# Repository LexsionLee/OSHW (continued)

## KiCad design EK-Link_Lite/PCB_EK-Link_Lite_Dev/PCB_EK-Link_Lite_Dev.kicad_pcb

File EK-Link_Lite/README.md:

# EK-Link Lite

此项目的目标是做一个引出部分IO到尾部，以实现制作一个某Link调试器的效果。灵感来源于网友们使用STM32最小系统板通过杜邦线连接某MCU进行调试，所以闲暇之余画了两张板。注意，EK-Link Lite是普通的双面板，而引出其他IO的Dev开发板是四层板。

该项目MCU采用的STM32F103CBT6，偶然翻出几年前留下的几枚MCU也是画这板子的原因之一。该板设计了RST按键，并引出了BOOT0、BOOT1以及SWD调试接口，同时为了迎合时代发展，USB采用了Type C接口。

## 效果图：

### EK-Link Lite

**实物：**

**3D：**

### EK-Link Lite Dev

## 基本信息：

### EK-Link Lite:

| 项目名称  | EK-Link Lite   |
| --------- | -------------- |
| PCB工艺   | 双面玻纤板     |
| PCB数量   | 1              |
| PCB尺寸   | 约59 * 23 (mm) |
| KiCad版本 | 5.1.9          |

### EK-Link Lite Dev:
| 项目名称  | EK-Link Lite Dev   |
| --------- | -------------- |
| PCB工艺   | 四层玻纤板 |
| PCB数量   | 1              |
| PCB尺寸   | 约59 * 23 (mm) |
| KiCad版本 | 5.1.9          |

## 其他事项：

暂无。

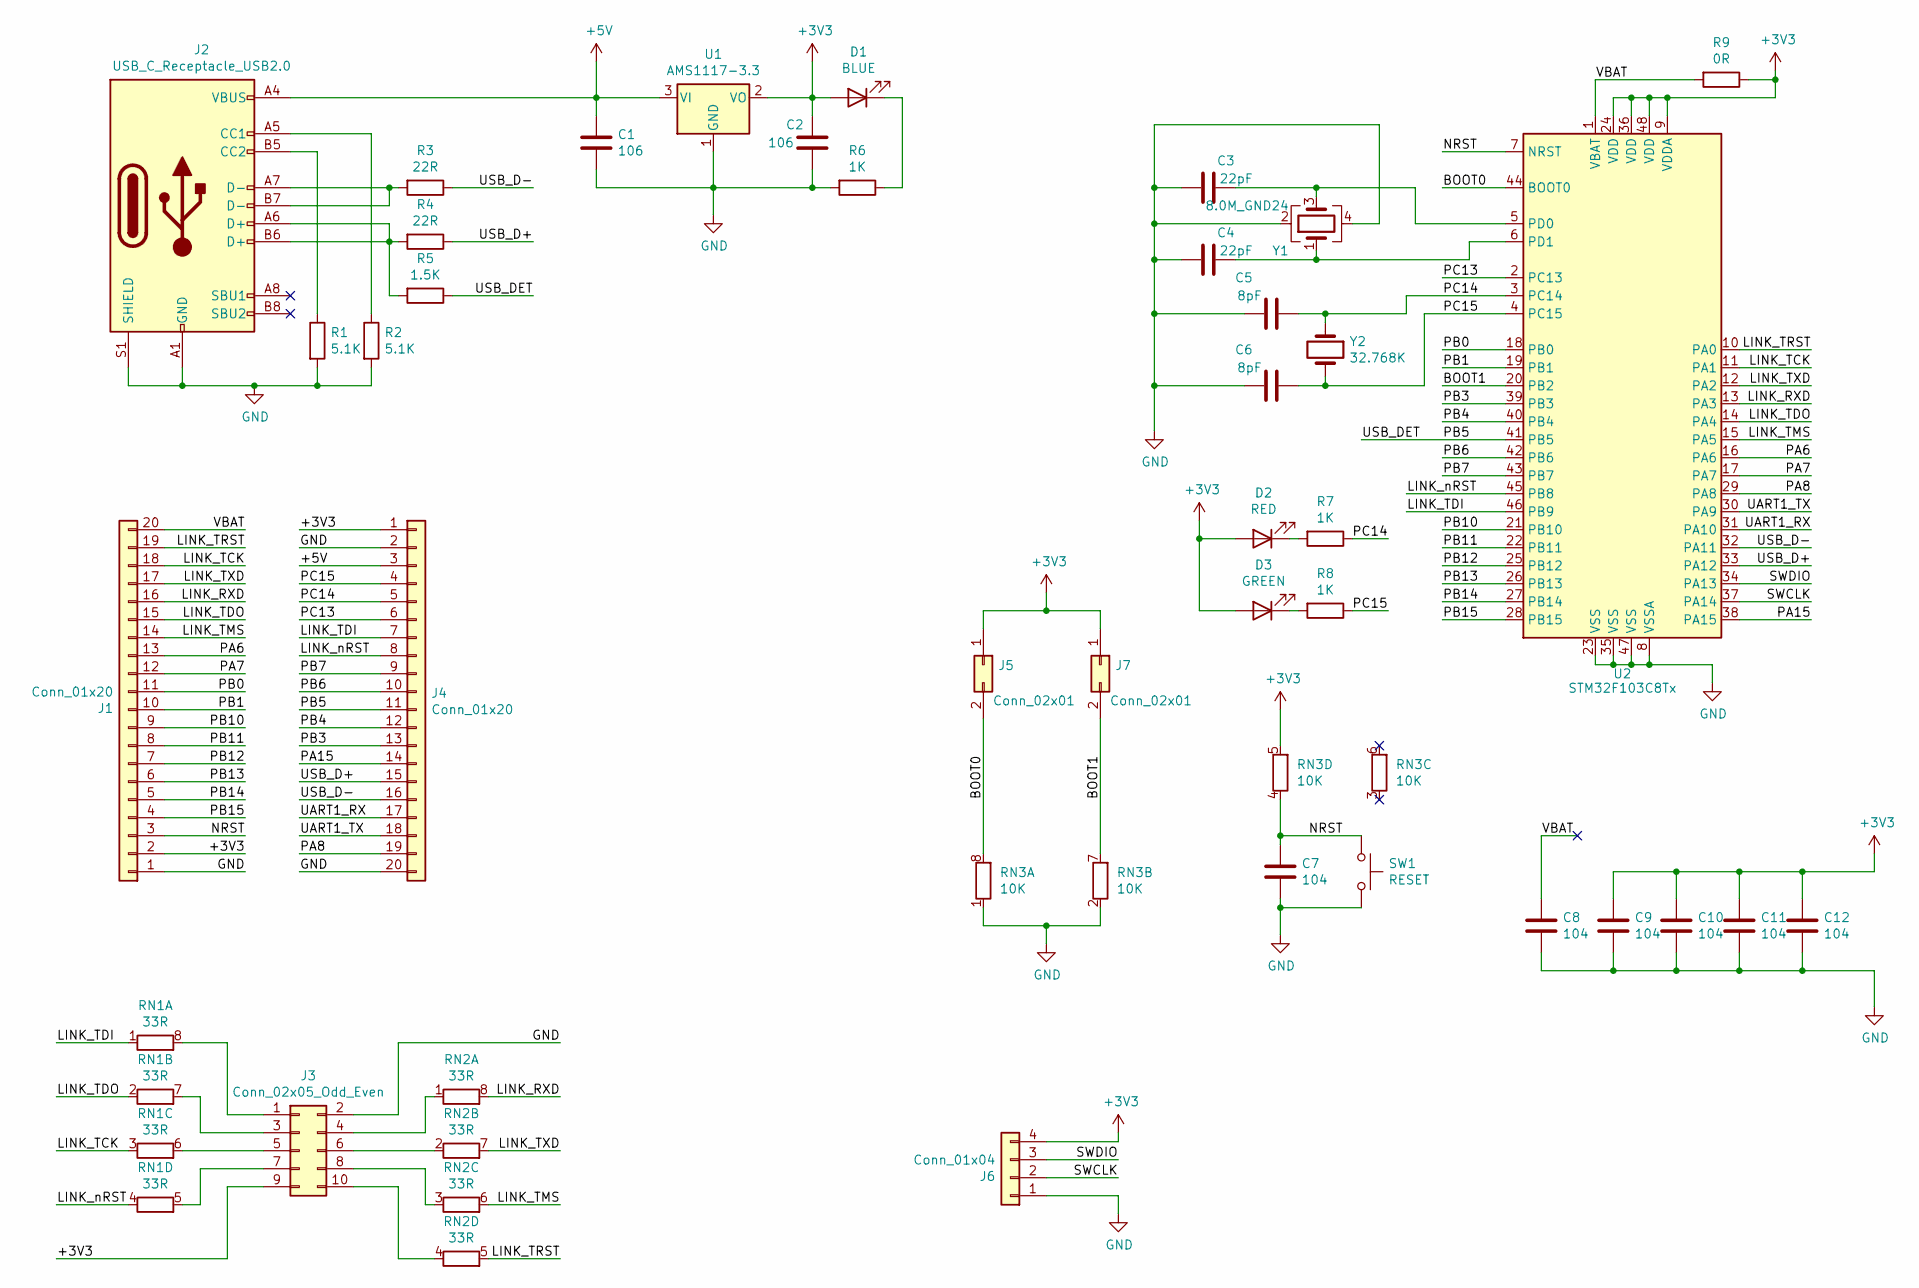
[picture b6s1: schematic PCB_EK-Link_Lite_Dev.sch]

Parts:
C1, C2: 106; C_0805_2012Metric
C3, C4: 22pF; C_0603_1608Metric
C5, C6: 8pF; C_0603_1608Metric
C7, C8, C9, C10, C11, C12: 104; C_0603_1608Metric
D1: BLUE; LED_0603_1608Metric
D2: RED; LED_0603_1608Metric
D3: GREEN; LED_0603_1608Metric
J1, J4: Conn_01x20; PinHeader_1x20_P2.54mm_Vertical
J2: USB_C_Receptacle_USB2.0; USB_C_Receptacle_Palconn_UTC16-G
J3: Conn_02x05_Odd_Even; Link_JTAG_10Pin
J5, J7: Conn_02x01; PinHeader_2x01_P2.54mm_Vertical
J6: Conn_01x04; PinHeader_1x04_P2.54mm_Vertical
R1, R2: 5.1K; R_0603_1608Metric
R3, R4: 22R; R_0402_1005Metric
R5: 1.5K; R_0603_1608Metric
R6, R7, R8: 1K; R_0603_1608Metric
R9: 0R; R_0603_1608Metric
RN1, RN2: 33R; R_Array_Concave_4x0603
RN3: 10K; R_Array_Concave_4x0603
SW1: RESET; SW_Push_SPST_NO_Alps_SKRK
U1: AMS1117-3.3; SOT-223-3_TabPin2
U2: STM32F103C8Tx; LQFP-48_7x7mm_P0.5mm
Y1: 8.0M_GND24; Oscillator_SMD_TXC_7C-4Pin_5.0x3.2mm_HandSoldering
Y2: 32.768K; Crystal_SMD_G8-2Pin_3.2x1.5mm_HandSoldering

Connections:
+3V3: C2.1, C9.1, C10.1, C11.1, C12.1, D1.2 (A), D2.2 (A), D3.2 (A), J1.2, J3.9, J4.1, J5.1, J6.4, J7.1, R9.1, RN3.5 (R4.2), U1.2 (VO), U2.9 (VDDA), U2.24 (VDD), U2.36 (VDD), U2.48 (VDD)
+5V: C1.1, J2.A4 (VBUS), J2.A9 (VBUS), J2.B4 (VBUS), J2.B9 (VBUS), J4.3, U1.3 (VI)
/BOOT0: J5.2, RN3.8 (R1.2), U2.44 (BOOT0)
/BOOT1: J7.2, RN3.7 (R2.2), U2.20 (PB2)
/LINK_RXD: J1.16, RN2.8 (R1.2), U2.13 (PA3)
/LINK_TCK: J1.18, RN1.3 (R3.1), U2.11 (PA1)
/LINK_TDI: J4.7, RN1.1 (R1.1), U2.46 (PB9)
/LINK_TDO: J1.15, RN1.2 (R2.1), U2.14 (PA4)
/LINK_TMS: J1.14, RN2.6 (R3.2), U2.15 (PA5)
/LINK_TRST: J1.19, RN2.5 (R4.2), U2.10 (PA0)
/LINK_TXD: J1.17, RN2.7 (R2.2), U2.12 (PA2)
/LINK_nRST: J4.8, RN1.4 (R4.1), U2.45 (PB8)
/NRST: C7.1, J1.3, RN3.4 (R4.1), SW1.1, U2.7 (NRST)
/PA6: J1.13, U2.16 (PA6)
/PA7: J1.12, U2.17 (PA7)
/PA8: J4.19, U2.29 (PA8)
/PA15: J4.14, U2.38 (PA15)
/PB0: J1.11, U2.18 (PB0)
/PB1: J1.10, U2.19 (PB1)
/PB3: J4.13, U2.39 (PB3)
/PB4: J4.12, U2.40 (PB4)
/PB5: J4.11, R5.1, U2.41 (PB5)
/PB6: J4.10, U2.42 (PB6)
/PB7: J4.9, U2.43 (PB7)
/PB10: J1.9, U2.21 (PB10)
/PB11: J1.8, U2.22 (PB11)
/PB12: J1.7, U2.25 (PB12)
/PB13: J1.6, U2.26 (PB13)
/PB14: J1.5, U2.27 (PB14)
/PB15: J1.4, U2.28 (PB15)
/PC13: J4.6, U2.2 (PC13)
/PC14: C5.2, J4.5, R7.1, U2.3 (PC14), Y2.1
/PC15: C6.2, J4.4, R8.1, U2.4 (PC15), Y2.2
/SWCLK: J6.2, U2.37 (PA14)
/SWDIO: J6.3, U2.34 (PA13)
/UART1_RX: J4.17, U2.31 (PA10)
/UART1_TX: J4.18, U2.30 (PA9)
/USB_D+: J4.15, R4.1, U2.33 (PA12)
/USB_D-: J4.16, R3.1, U2.32 (PA11)
/VBAT: C8.1, J1.20, R9.2, U2.1 (VBAT)
GND: C1.2, C2.2, C3.1, C4.1, C5.1, C6.1, C7.2, C8.2, C9.2, C10.2, C11.2, C12.2, J1.1, J2.A1 (GND), J2.A12 (GND), J2.B1 (GND), J2.B12 (GND), J2.S1 (SHIELD), J3.2, J4.2, J4.20, J6.1, R1.2, R2.2, R6.2, RN3.1 (R1.1), RN3.2 (R2.1), SW1.2, U1.1 (GND), U2.8 (VSSA), U2.23 (VSS), U2.35 (VSS), U2.47 (VSS), Y1.2, Y1.4
unnamed: C3.2, U2.5 (PD0), Y1.3
unnamed: C4.2, U2.6 (PD1), Y1.1
unnamed: D1.1 (K), R6.1
unnamed: D2.1 (K), R7.2
unnamed: D3.1 (K), R8.2
unnamed: J2.A5 (CC1), R2.1
unnamed: J2.A6 (D+), J2.B6 (D+), R4.2, R5.2
unnamed: J2.A7 (D-), J2.B7 (D-), R3.2
unnamed: J2.B5 (CC2), R1.1
unnamed: J3.1, RN1.8 (R1.2)
unnamed: J3.3, RN1.7 (R2.2)
unnamed: J3.4, RN2.1 (R1.1)
unnamed: J3.5, RN1.6 (R3.2)
unnamed: J3.6, RN2.2 (R2.1)
unnamed: J3.7, RN1.5 (R4.2)
unnamed: J3.8, RN2.3 (R3.1)
unnamed: J3.10, RN2.4 (R4.1)

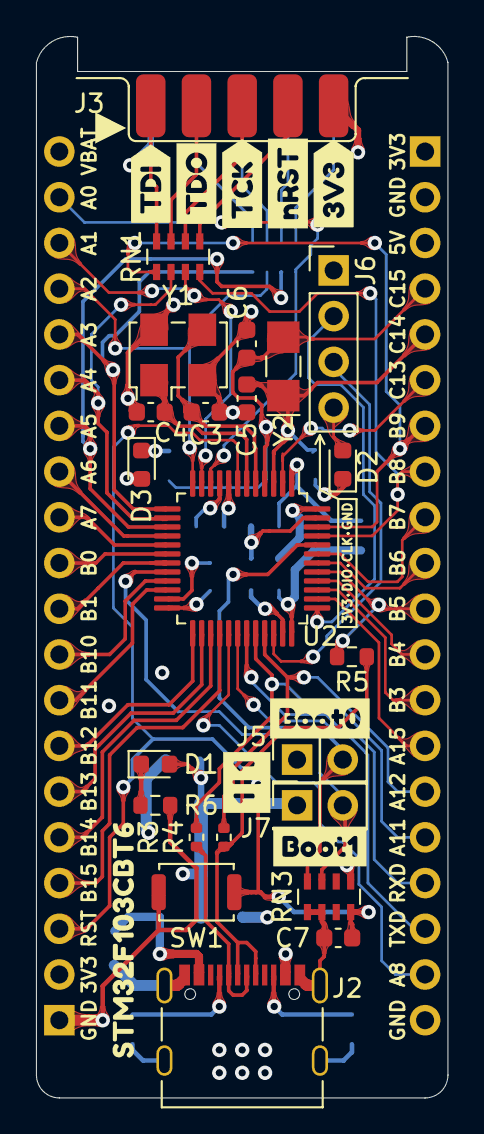
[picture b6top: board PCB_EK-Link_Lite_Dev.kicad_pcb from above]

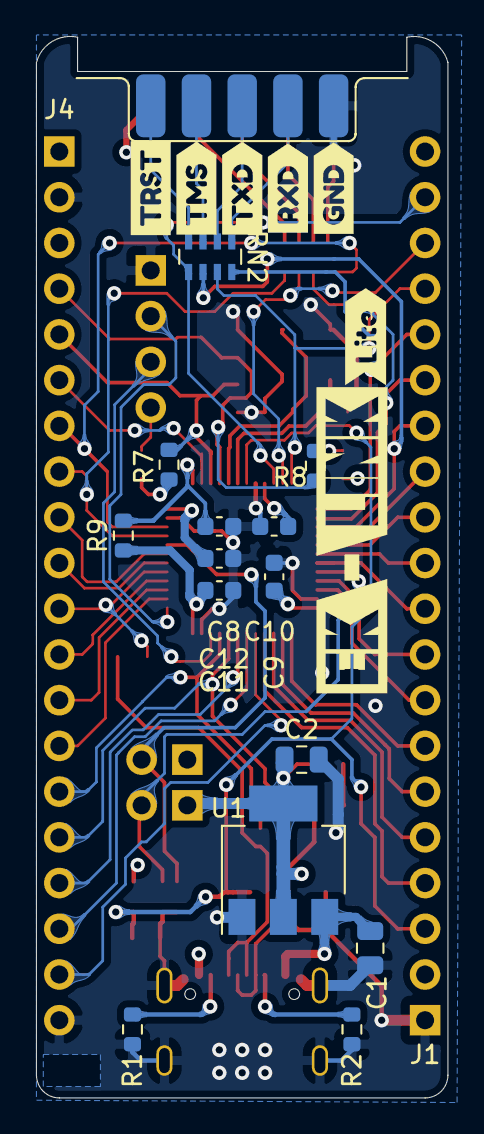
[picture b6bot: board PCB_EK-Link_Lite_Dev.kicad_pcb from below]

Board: 4 copper layers, 22.9 x 59.0 mm, 57 parts (25 on the bottom side), 58 nets.

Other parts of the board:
svg2mod, svg2mod#2, svg2mod#3, svg2mod#4, svg2mod#5, svg2mod#6, svg2mod#7, svg2mod#8, svg2mod#9, svg2mod#10, svg2mod#11, svg2mod#12, svg2mod#13, svg2mod#14, svg2mod#15, svg2mod#16, svg2mod#17, svg2mod#18: G***; label

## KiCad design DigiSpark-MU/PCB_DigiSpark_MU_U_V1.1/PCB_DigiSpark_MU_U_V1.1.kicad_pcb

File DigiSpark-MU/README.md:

# DigiSpark-MU

此项目仿制了Digistump 的 Digispark，它是一款基于ATtiny85的单片机开发板，类似于Arduino，但它更便宜、更小巧，性能也相对弱一些。通过为其编程，可模拟HID设备（如键盘），从而欺骗电脑使其认为是人在操作它，这类应用称为BadUSB。具体相关内容可以通过网络查询，此处不再赘述。

此项目命名为DigiSpark-MU，是因为对比原始项目，本项目单片机选用了QFN封装的ATtiny85-20MU而不是SOIC封装的SU。因为全球IC价格上涨的关系，SOIC封装的tiny85价格相对更高。而使用QFN封装的IC，不但价格更低，且得益于其不到1毫米的封装厚度，有望实现将芯片隐藏于层叠的PCB中。这样便可以得到比原始设计更小、更薄的设计。为了实现薄化设计，此项目舍弃了为其他电压应用准备的5V LDO，舍弃了USB取电处的防逆流二极管。

> 我才不会说是因为白嫖了立创海外代购51减50活动，Digi-Key的单片机真香。

## 效果图：

### 实物图：

### M板：

### U板（上板）：

## 基本信息：

| 项目名称  | DigiSpark-MU            |
| --------- | ----------------------- |
| PCB工艺   | 双面玻纤板              |
| PCB数量   | 2                       |
| PCB尺寸   | 约26.8 * 12 (mm)  *2PCS |
| KiCad版本 | 5.1.9                   |

## 其他事项：

PCB厚度是1.0mm。

该项目由两片PCB组成。元器件主要集中在下板上，我称其为M板；USB接触的金手、齐纳二极管指和复位按键在上板，称其为U板。项目文件有三个，ALL是所有元器件在一个原理图中，为了提供统一的原理图；M是底层PCB的设计；U是上层板的设计。Gerber文件压缩存放于对应PCB目录的Gerber目录下。

装配方式为两枚PCB分别回流焊，然后再将两枚PCB通过回流焊叠焊在一起。

其他未尽事项请参阅原始文件。

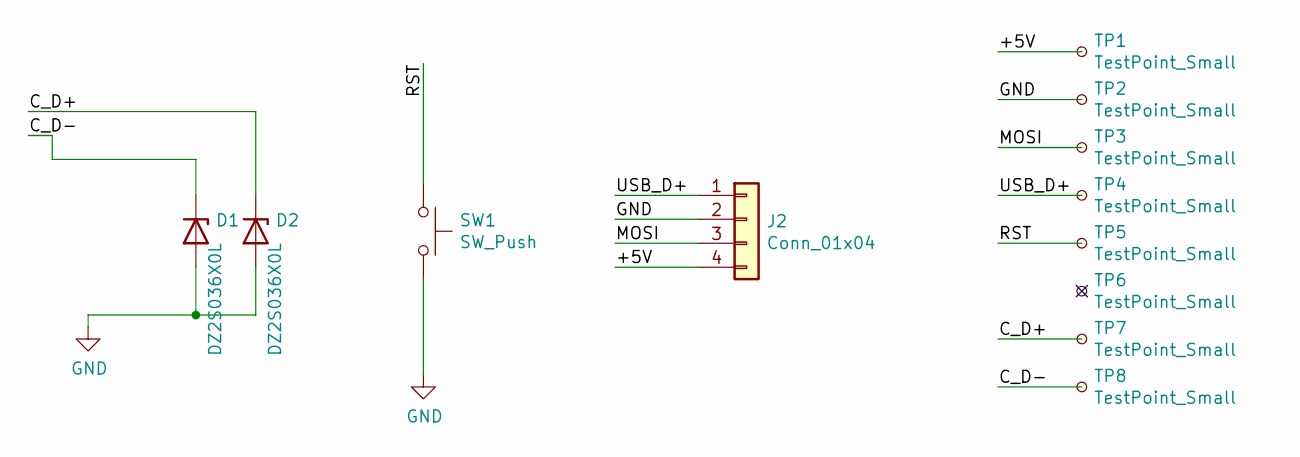
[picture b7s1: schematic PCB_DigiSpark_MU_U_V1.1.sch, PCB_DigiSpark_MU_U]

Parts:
D1, D2: DZ2S036X0L; D_SOD-523
J2: Conn_01x04; Lex_Conn_Edge_2.54-4
SW1: SW_Push; SW_SPST_SKQG_WithStem
TP1, TP2, TP3, TP4, TP5, TP6, TP7, TP8: TestPoint_Small; TestPoint_Pad_D1.0mm

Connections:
+5V: J2.4, TP1.1; also elsewhere on the board
/C_D+: D2.1 (K), TP7.1; also elsewhere on the board
/C_D-: D1.1 (K), TP8.1; also elsewhere on the board
/MOSI: J2.3, TP3.1
/RST: SW1.1, TP5.1
/USB_D+: J2.1, TP4.1
GND: D1.2 (A), D2.2 (A), J2.2, SW1.2, TP2.1; also elsewhere on the board

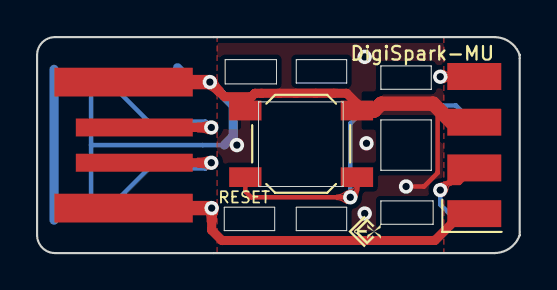
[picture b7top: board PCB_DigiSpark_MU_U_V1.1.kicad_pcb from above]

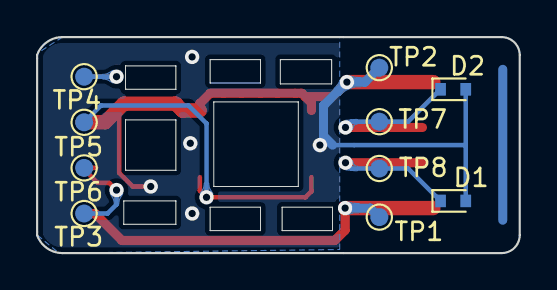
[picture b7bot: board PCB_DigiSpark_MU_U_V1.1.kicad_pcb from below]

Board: 2 copper layers, 26.8 x 12.0 mm, 13 parts (10 on the bottom side), 7 nets.

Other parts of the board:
J1: USB_A; PCBUSB_A_Male

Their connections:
+5V: J1.1; also elsewhere on the board
/C_D+: J1.3; also elsewhere on the board
/C_D-: J1.2; also elsewhere on the board
GND: J1.4; also elsewhere on the board

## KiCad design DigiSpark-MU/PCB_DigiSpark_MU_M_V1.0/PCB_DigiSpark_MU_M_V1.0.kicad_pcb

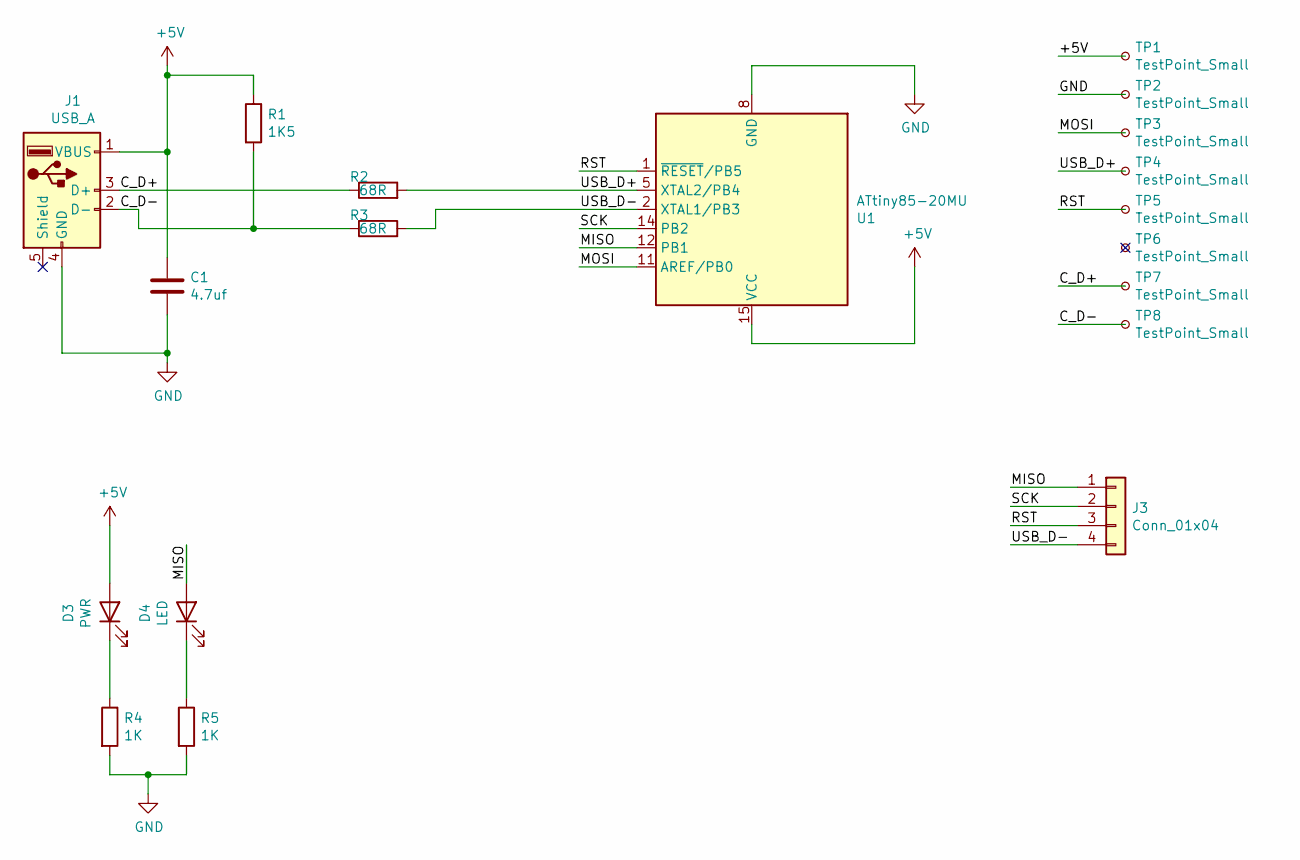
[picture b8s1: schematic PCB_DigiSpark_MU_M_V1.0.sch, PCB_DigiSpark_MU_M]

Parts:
C1: 4.7uf; C_0603_1608Metric
D3: PWR; LED_0603_1608Metric
D4: LED; LED_0603_1608Metric
J1: USB_A; PCBUSB_A_Male
J3: Conn_01x04; Lex_Conn_Edge_2.54-4
R1: 1K5; R_0603_1608Metric
R2, R3: 68R; R_0603_1608Metric
R4, R5: 1K; R_0603_1608Metric
TP1, TP2, TP3, TP4, TP5, TP6, TP7, TP8: TestPoint_Small; TestPoint_Pad_D1.0mm
U1: ATtiny85-20MU; QFN-20-1EP_4x4mm_P0.5mm_EP2.6x2.6mm

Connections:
+5V: C1.1, D3.2 (A), J1.1 (VBUS), R1.1, TP1.1, U1.15 (VCC)
/C_D+: J1.3 (D+), R2.1, TP7.1
/C_D-: J1.2 (D-), R1.2, R3.1, TP8.1
/MISO: D4.2 (A), J3.1, U1.12 (PB1)
/MOSI: TP3.1, U1.11 (AREF/PB0)
/RST: J3.3, TP5.1, U1.1 (~RESET~/PB5)
/SCK: J3.2, U1.14 (PB2)
/USB_D+: R2.2, TP4.1, U1.5 (XTAL2/PB4)
/USB_D-: J3.4, R3.2, U1.2 (XTAL1/PB3)
GND: C1.2, J1.4 (GND), R4.2, R5.2, TP2.1, U1.8 (GND), U1.21 (GND)
unnamed: D3.1 (K), R4.1
unnamed: D4.1 (K), R5.1

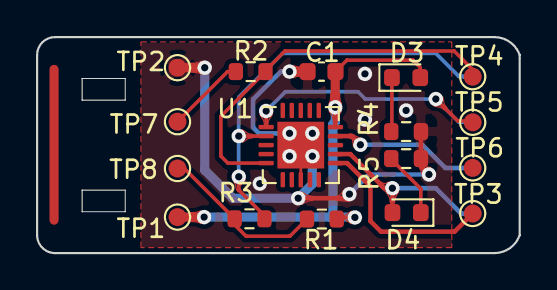
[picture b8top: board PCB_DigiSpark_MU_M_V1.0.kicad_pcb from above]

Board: 2 copper layers, 26.8 x 12.0 mm, 18 parts (1 on the bottom side), 12 nets.

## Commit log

2021-10-27 add DigiSpark-MU
2021-10-27 fix silks
2021-12-14 add EK-Link Lite
2021-12-14 Fix layer mark
2021-12-19 Fix RESET Key Silk.
2022-01-18 Add Real Photo
2022-01-22 Add project OLED64128Module_OEL1M4033FPC-A1-E
2022-01-22 Modifide README,The last was fault.
2022-01-25 test OK.
2022-01-25 Add Teardrop
2022-02-18 add Board DAP_Link_CH55xT
2022-02-19 add Board TFT80160
2022-02-25 Fix Silk for SW-GND&SW-RST at front.
2022-04-08 DAP_Link_CH55xT:update README.md
2022-04-10 F401CCU6_Dev added.
2022-04-17 F401CCU6:Fix README.md
2022-04-24 USBC_PD_TEST:Added
